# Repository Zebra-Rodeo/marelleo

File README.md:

# Marelleo

**English** · [Français](README.fr.md)

A box that plays a story when a child puts a figurine on top. No screen, no
account, no subscription, and nothing that leaves the house.

I built it for my three kids knowing nothing about electronics when I started.
Everything is here to rebuild it: the files to print, the board's manufacturing
files, the code, and enough guidance to get through it if you have never
soldered.

The story of the project, mistakes included, is written up here:
**[zebra.rodeo/en/blog/marelleo](https://zebra.rodeo/en/blog/marelleo/)**

---

## What it does

An NFC sticker is glued under a figurine. You put it on the engraved circle,
the box reads the sticker and plays whatever is associated with it: a file, a
list of files, or a live radio stream. Take the figurine off and the sound
carries on, or stops, depending on the setting.

Everything is configured from a browser, on the home WiFi, at
`http://marelleo.local`. Nothing to install. The box fetches its own updates.

| Gesture | Effect |
|---|---|
| Put a figurine on | plays its list |
| Put the same one back | resumes if it was paused |
| Short press | pause, resume, or restart a finished list |
| Long press | next track |
| Knob | volume, and power off at the click at the bottom of its travel |

Formats played: MP3 and M4A. The stories live on a microSD card.

---

## Two ways to build it

**On breadboard and perfboard**, with off-the-shelf modules. This is where to
start: you get it wrong, you unplug, you start again, and nothing is damaged.
Not a single solder joint for the first version.

**On the printed board**, whose manufacturing files are in [`carte/`](carte/).
Five assembled boards cost about 160 euros from JLCPCB, so 32 euros a board
with components placed. It is cleaner, smaller, and it lasts.

The same firmware runs on both: `pio run -e boite` for the modules,
`pio run -e carte` for the printed board.

---

## What to buy

### Module version, to start with

| Role | Part | Ballpark price |
|---|---|---|
| Brains | [ESP32-S3-DevKitC-1](https://www.amazon.fr/s?k=esp32+s3+devkitc) **N16R8** | 15 € |
| NFC reader | PN532, the red board, **in serial mode (HSU)** | 10 € |
| Audio | MAX98357A, I2S converter and amplifier | 7 € |
| Speaker | Visaton FRS 7, 4 Ω | 15 € |
| Power | Lipo Rider Plus, or any 5 V charging module | 12 € |
| Volume | 10 kΩ potentiometer **with a switch** | 3 € |
| Tags | NTAG213 25 mm, **on-metal** type | 10 € for 20 |
| Prototyping | [breadboard](https://www.amazon.fr/s?k=breadboard) and Dupont wires | 10 € |

The PN532 ships configured for I2C: there are two small switches on the board,
set them to **HSU**. It is printed on the back.

### Pinout, module version

| GPIO | To |
|---|---|
| `4` | amplifier `SD`, mutes the hiss at idle |
| `5` `6` `7` | amplifier `BCLK` `LRC` `DIN` |
| `8` `9` | PN532 `TXD` `RXD` |
| `11` `12` `13` `14` | SD card `CS` `SCK` `MOSI` `MISO` |
| `10` | potentiometer wiper, **must be on ADC1** |
| `18` | button |
| `48` | onboard LED |

The potentiometer has to sit on an ADC1 pin, that is to say `1` to `10`: the
ESP32-S3's ADC2 goes mute as soon as WiFi comes up, and the volume starts
jumping around for no visible reason.

---

## The enclosure

Three parts in [`boitier/`](boitier/), to print in PLA:

| File | Size | Notes |
|---|---|---|
| `marelleo-corps.stl` | 120 × 120 × 80 mm | the cube, raised name and engraved landing circle |
| `marelleo-base.stl` | 120 × 120 × 29 mm | the bottom, which carries the board and the battery |
| `marelleo-molette.stl` | 24 × 24 × 12 mm | the volume knob |

Printed on a Bambu Lab A1, 0.4 nozzle, 0.2 layers, three walls, 15 % infill.
The body goes on the plate open face up: no supports needed.

The PN532's antenna sits right under the engraved circle. Its range goes
through 3 mm of PLA without trouble.

**Do not screw straight into the plastic.** It holds once, twice, and on the
third go the part splits along the layers. Use **M3 brass inserts**: set one on
the hole, come down on it with the tip of the soldering iron, the brass melts
the plastic around itself and sinks in. You get a metal thread you can undo a
hundred times.

---

## The board

Everything is in [`carte/`](carte/):

- `marelleo-gerbers.zip`: upload as is to the manufacturer;
- `fab/marelleo-bom.csv` and `fab/marelleo-cpl.csv`: so JLCPCB can place the
  components;
- `composants.csv`: the readable list, with LCSC part numbers;
- `marelleo.kicad_pcb`: the board itself, if you want to modify it;
- `generer.py`: the script that draws it, because the board is generated
  rather than clicked;
- [`schema.md`](carte/schema.md): **read this before ordering.** The choices,
  the bench measurements, and the traps that cost me evenings.

Order from [JLCPCB](https://jlcpcb.com/): four layers, 1.6 mm, assembly on the
top side, standard and extended parts. Check LCSC stock on the day you order,
`stock.py` does it for you.

Two known deviations are documented in `schema.md`, including the `D1` diode
whose rotation has to be corrected by 180 degrees in their preview. Read it.

---

## The firmware

**It is written for this exact build.** The pinout lives in the code, not in a
configuration file: the two environments match my printed board and my module
prototype, and nothing else. If you wire it differently, a moved wire means a
constant to change at the top of `src/main.cpp`, and until that is done it will
not work, sometimes without saying anything. Start by reproducing the pinout
given above, and only move it afterwards.

And this is a weekend project, not a product. It runs every day at my house,
which is a sample of one box. There are rough edges left, cases nobody has run
into, and things I would do differently if I rewrote it. Read it as a starting
point that works, not as a reference.

[PlatformIO](https://platformio.org/) does all the work.

```sh
cd firmware
pio run -e boite -t upload     # modules on perfboard
pio run -e carte -t upload     # printed board
pio device monitor
```

Both environments compile the same code. What changes is the pinout, the flash
size and the PSRAM type, and mixing them up gives you a board that does not
start at all: `carte/schema.md` explains why.

### First start-up

The box knows no network when first powered on, so **it opens its own**, named
`Marelleo-XXXX`. A phone that connects to it brings up the setup page on its
own, like in a hotel. You pick the home WiFi there, and the box restarts on it.

After that, `http://marelleo.local` from any device on the network.

Button held for three seconds at power-on: the WiFi credentials are erased and
the box reopens its portal. That is the way out for a box that moves house, or
that you give away.

### Updates

The firmware compiled here fetches the versions published on
`maj.marelleo.org`, which are mine. A new version gets three start-ups to prove
itself: if it cannot find the network, the box goes back to the previous one on
its own.

**If you modify the code, change `MAJ_SOURCE_DEFAUT` in
`firmware/src/version.h`**, otherwise the box will replace your version with
mine at the first check.

---

## The figurines

Any object will do: a wooden figure, a toy car, a token, a flat pebble. Glue a
25 mm NTAG213 tag under its feet, the **on-metal** type if the object contains
any metal.

Put the figurine on the box, open `http://marelleo.local`, and it appears at
the top of the list. Give it a name, send files or search for a podcast, and
that is it. A figurine carries stories or a radio, never both.

---

## Licence

MIT, for the code as well as the manufacturing files. Build it, change it, sell
it, give it away. If you make something out of it, I would love to see it.

Marelleo, from *marelle*, the French word for hopscotch, the game where you
move forward by putting a foot down on a square. But mostly from **Mar**ceau,
**Ell**a and L**éo**nie, to whom the box belongs.

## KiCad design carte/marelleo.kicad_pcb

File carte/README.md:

# The board

**English** · [Français](README.fr.md)

Four layers, 1.6 mm, 60 × 70 mm. The files are ready to order.

| File | Role |
|---|---|
| `marelleo-gerbers.zip` | upload as is to the manufacturer |
| `fab/marelleo-bom.csv` | the bill of materials, JLCPCB format |
| `fab/marelleo-cpl.csv` | the component positions, JLCPCB format |
| `composants.csv` | the same list, readable, with LCSC part numbers |
| `marelleo.kicad_pcb` | the board itself, to modify it |
| `generer.py` | the script that draws it: the board is generated, not clicked |
| `stock.py` | checks LCSC stock on the day you order |
| `schema.md` | **read it before ordering** |

`schema.md` carries the choices, the measurements taken at the bench and the
traps that cost me evenings: the charger that suspends charging when you turn
the box off, the NFC module that blinks instead of starting, the diode whose
rotation has to be corrected by 180 degrees in JLCPCB's preview.

Five assembled boards came to about 160 euros, so 32 euros a board with
components placed.

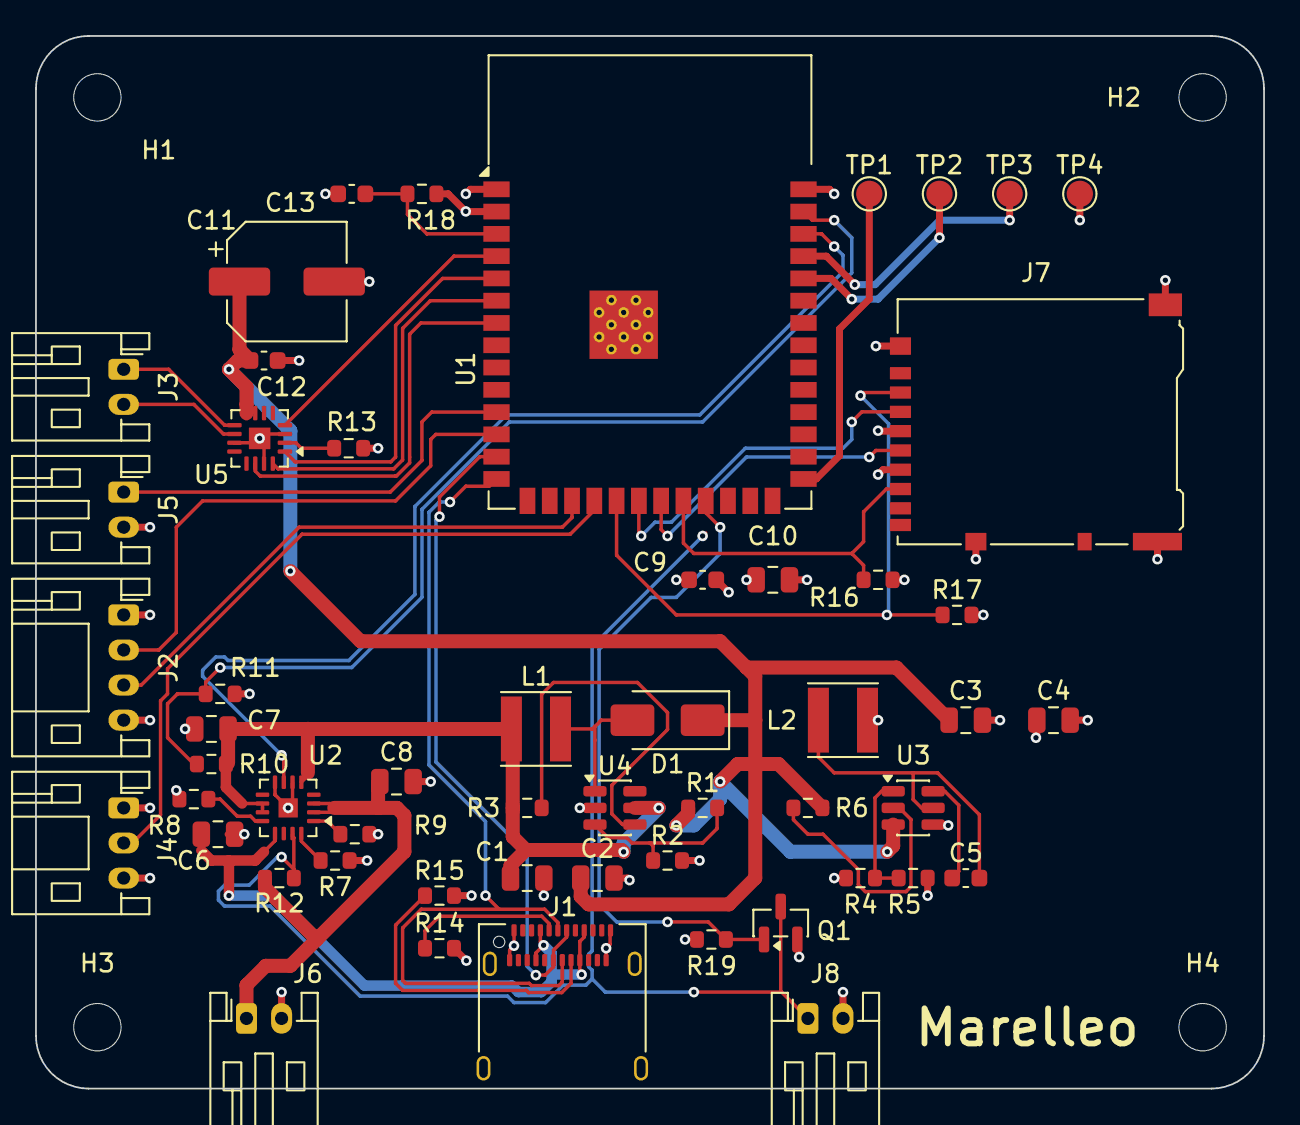
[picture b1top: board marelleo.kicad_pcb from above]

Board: 4 copper layers, 70.0 x 60.0 mm, 57 parts (0 on the bottom side), 43 nets.

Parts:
C1, C2, C4: 22 uF; C_0805_2012Metric
C3, C6, C7, C8, C10: 10 uF; C_0805_2012Metric
C5, C9, C12: 100 nF; C_0603_1608Metric
C11: 470 uF; CP_Elec_6.3x7.7
C13: 1 uF; C_0603_1608Metric
D1: SS34; D_SMA
H1, H2, H3, H4: M2.5; MountingHole_2.7mm_M2.5
J1: USB-C, charge et mise a jour; USB_C_Receptacle_Amphenol_12401610E4-2A
J2: vers le lecteur NFC deporte; JST_PH_S4B-PH-K_1x04_P2.00mm_Horizontal
J3: haut-parleurs; JST_PH_S2B-PH-K_1x02_P2.00mm_Horizontal
J4: potentiometre de volume; JST_PH_S3B-PH-K_1x03_P2.00mm_Horizontal
J5: bouton; JST_PH_S2B-PH-K_1x02_P2.00mm_Horizontal
J6: batterie; JST_PH_S2B-PH-K_1x02_P2.00mm_Horizontal
J7: connecteur microSD; microSD_HC_Hirose_DM3AT-SF-PEJM5
J8: interrupteur du potentiometre; JST_PH_S2B-PH-K_1x02_P2.00mm_Horizontal
L1, L2: 4,7 uH; L_Taiyo-Yuden_MD-4040
Q1: 2N7002; SOT-23
R1: 75 k; R_0603_1608Metric
R2, R9, R16, R17, R18: 10 k; R_0603_1608Metric
R3, R6, R10, R11, R19: 100 k; R_0603_1608Metric
R4: 0 R; R_0603_1608Metric
R5, R13: NP; R_0603_1608Metric
R7: 1 k; R_0603_1608Metric
R8: 1,5 k; R_0603_1608Metric
R12: 1 M; R_0603_1608Metric
R14, R15: 5,1 k; R_0603_1608Metric
TP1: TEST_IO0; TestPoint_Pad_D1.5mm
TP2: TEST_RX; TestPoint_Pad_D1.5mm
TP3: TEST_TX; TestPoint_Pad_D1.5mm
TP4: GND; TestPoint_Pad_D1.5mm
U1: ESP32-S3-WROOM-1-N8R2; ESP32-S3-WROOM-1
U2: BQ24075RGT, chargeur a chemin d'alimentation; VQFN-16-1EP_3x3mm_P0.5mm_EP1.1x1.1mm
U3: AP63203WU, abaisseur 3V3; TSOT-23-6
U4: MT3608, elevateur 5V; SOT-23-6
U5: MAX98357A; TQFN-16-1EP_3x3mm_P0.5mm_EP1.23x1.23mm

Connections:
+3V3: C4.1, C9.1, C10.1, J2.1, J4.1, J7.4, L2.2, R4.1, R16.2, R17.2, R18.2, U1.2
+5V: C2.1, C3.1, C11.1, C12.1, D1.1, R1.1, R6.2, U3.3, U5.7, U5.8
AMPLI_ARRET: U1.4, U5.4
AMPLI_GAIN: R13.1, U5.2
ARRET: J8.1, Q1.3, R12.1, U2.15
ARRET_CMD: Q1.1, R19.1, U1.23
BOUTON: J5.1, U1.11
BST_3V3: C5.1, U3.6
EN_3V3: R6.1, U3.2
EN_5V: R3.1, U4.4
FB_3V3: R4.2, R5.1, U3.1
FB_5V: R1.2, R2.1, U4.3
GND: C1.2, C2.2, C3.2, C4.2, C6.2, C7.2, C8.2, C9.2, C10.2, C11.2, C12.2, C13.2, J1.A1, J1.A12, J1.B1, J1.B12, J1.SH, J2.4, J4.3, J5.2, J6.2, J7.6, J7.SH, J8.2, Q1.2, R2.2, R5.2, R7.2, R8.2, R9.2, R11.2, R13.2, R14.2, R15.2, R19.2, TP4.1, U1.1, U1.40, U1.41, U2.6, U2.8, U2.17, U3.4, U4.2, U5.3, U5.11, U5.15, U5.17
HP_MOINS: J3.2, U5.10
HP_PLUS: J3.1, U5.9
I2S_BCLK: U1.6, U5.16
I2S_DIN: U1.5, U5.1
I2S_LRCLK: U1.7, U5.14
ILIM: R8.1, U2.12
ISET: R7.1, U2.16
NFC_RX: J2.2, U1.12
NFC_TX: J2.3, U1.17
NIVEAU_BATTERIE: R10.2, R11.1, U1.39
RESET: C13.1, R18.1, U1.3
SD_CLK: J7.5, U1.21
SD_CS: J7.2, R17.1, U1.19
SD_MISO: J7.7, R16.1, U1.22
SD_MOSI: J7.3, U1.20
SW_3V3: C5.2, L2.1, U3.5
SW_5V: D1.2, L1.2, U4.1
TEST_IO0: TP1.1, U1.27
TEST_RX: TP2.1, U1.36
TEST_TX: TP3.1, U1.37
TS: R9.1, U2.1
USB_CC1: J1.A5, R14.1
USB_CC2: J1.B5, R15.1
USB_D+: J1.A6, J1.B6, U1.14
USB_D-: J1.A7, J1.B7, U1.13
USB_PRESENT: U1.38, U2.7
VBAT: C8.1, J6.1, R12.2, U2.2, U2.3
VBUS: C6.1, J1.A4, J1.A9, J1.B4, J1.B9, U2.13
VOLUME: J4.2, U1.18
VSYS: C1.1, C7.1, L1.1, R3.2, R10.1, U2.5, U2.10, U2.11, U4.5

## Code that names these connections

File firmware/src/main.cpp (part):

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// Les GPIO 11 a 14 sont sur l'ADC2, que le WiFi rend muet. Sans importance ici :
// le bus SPI s'en sert en numerique, jamais en analogique.
#ifdef CARTE_IMPRIMEE
constexpr uint8_t PIN_SD_CS = 11, PIN_SD_CLK = 13, PIN_SD_MOSI = 12, PIN_SD_MISO = 14;
#else
constexpr uint8_t PIN_SD_CS = 11, PIN_SD_CLK = 12, PIN_SD_MOSI = 13, PIN_SD_MISO = 14;
#endif
SPIClass spiSD(FSPI);
fs::FS*  contenu = nullptr;
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
bool monterStockage() {
  bool flash = LittleFS.begin();
  spiSD.begin(PIN_SD_CLK, PIN_SD_MISO, PIN_SD_MOSI, PIN_SD_CS);
  // 4 MHz, 1 MHz en repli pour monter. Des ecritures echouent au hasard :
  // `sdCommand(): token error [13] 0x33`, une reponse corrompue a SEND_STATUS
  // juste apres l'ecriture des secteurs. Un bit se retourne sur le fil, le
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  // pas.
  bool monte = false;
  for (int essai = 1; essai <= 3 && !monte; essai++) {
    monte = SD.begin(PIN_SD_CS, spiSD, 4000000) || SD.begin(PIN_SD_CS, spiSD, 1000000);
    if (monte) break;
    Serial.printf("carte SD : montage refuse, essai %d sur 3\n", essai);
    SD.end();
    spiSD.end();
    delay(200);
    spiSD.begin(PIN_SD_CLK, PIN_SD_MISO, PIN_SD_MOSI, PIN_SD_CS);
  }
  if (monte) {
    contenu = &SD;       contenuSurSD = true;
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// pastilles. On l'active par -DCARTE_IMPRIMEE, voir l'environnement "carte"
// dans platformio.ini.
#ifdef CARTE_IMPRIMEE
constexpr uint8_t PIN_I2S_BCLK = 6, PIN_I2S_LRC = 7, PIN_I2S_DOUT = 5;
#else
constexpr uint8_t PIN_I2S_BCLK = 5, PIN_I2S_LRC = 6, PIN_I2S_DOUT = 7;
#endif
constexpr uint8_t PIN_AMP_SD   = 4;
constexpr uint8_t PIN_NFC_RX   = 8, PIN_NFC_TX = 9;
// La jauge n'existe que sur la carte imprimee : IO1 voit VSYS a travers un pont
// de deux 100 k, et IO2 recoit PGOOD du chargeur. Le prototype n'a ni l'un ni
// l'autre, d'ou 255, qui veut dire « pas de mesure » plutot qu'un chiffre faux.
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// Le verrou d'extinction : la grille de Q1, qui tire SYSOFF a la masse en
// parallele de l'interrupteur du potentiometre. Haut maintient la boite
// alimentee, bas la laisse s'eteindre.
constexpr uint8_t PIN_ARRET = 21;
#else
constexpr uint8_t PIN_BATTERIE = 255, PIN_USB = 255, PIN_ARRET = 255;
#endif
// Le potentiometre doit etre sur l'ADC1 (GPIO 1 a 10) : l'ADC2 de l'ESP32-S3
// devient muet des que le WiFi est actif.
constexpr uint8_t PIN_POT = 10, PIN_BOUTON = 18;   // GPIO 15, 16 et 17 libres
constexpr uint8_t PIN_LED      = 48;

// La mise en veille se decide sur le NIVEAU de volume, pas sur la valeur brute
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RTC_DATA_ATTR bool adieuDit = false;

Audio      audio;
Pn532Hsu   nfc(Serial1, PIN_NFC_RX, PIN_NFC_TX);
Library    biblio;
Commandes  commandes;
Batterie   batterie;
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String   dernierBadge;   // derniere figurine badgee, connue ou non : celle que la page configure
uint8_t  absences = 0;
uint32_t derniereScrutation = 0;
uint8_t  volume = 0;     // toujours dicte par la position du potentiometre

String enHex(const uint8_t* uid, uint8_t len) {
  char b[16] = {0};
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  SD.end();
  spiSD.end();
  delay(20);
  spiSD.begin(PIN_SD_CLK, PIN_SD_MISO, PIN_SD_MOSI, PIN_SD_CS);
  bool ok = SD.begin(PIN_SD_CS, spiSD, 4000000) || SD.begin(PIN_SD_CS, spiSD, 1000000);
  Serial.printf("carte SD : remontage %s\n", ok ? "reussi" : "echoue");
  return ok;
}
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    }
  }

  commandes.begin(PIN_POT, PIN_BOUTON, VOLUME_MIN, VOLUME_MAX);
  volume = commandes.volume();
  Serial.printf("volume : %u  [%u-%u]  brut %u\n",
                volume, VOLUME_MIN, VOLUME_MAX, commandes.potBrut());
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  if (volume > VOLUME_MIN) adieuDit = false;
  if (!adieuDit) {
    digitalWrite(PIN_AMP_SD, HIGH);
    carillon(PIN_I2S_BCLK, PIN_I2S_LRC, PIN_I2S_DOUT, volume, VOLUME_MAX);
    digitalWrite(PIN_AMP_SD, LOW);
  }

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    // pour verifier qu'un fichier est bien decode, sans bavarder le reste du temps.
    else if (m.e == Audio::evt_info && m.msg) Serial.printf("audio : %s\n", m.msg);
  };
  audio.setPinout(PIN_I2S_BCLK, PIN_I2S_LRC, PIN_I2S_DOUT);
  audio.setVolume(volume);
  xTaskCreatePinnedToCore(tacheAudio, "audio", 8192, nullptr, 4, nullptr, 1);

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  // WiFi pour revenir au portail de configuration. La LED passe au bleu pendant
  // l'attente, et au blanc quand l'effacement est confirme.
  bool effacer = false;
  pinMode(PIN_BOUTON, INPUT_PULLUP);
  if (digitalRead(PIN_BOUTON) == LOW) {
    led(0, 0, 30);
    uint32_t debut = millis();
    while (digitalRead(PIN_BOUTON) == LOW && millis() - debut < 3000) delay(20);
    effacer = millis() - debut >= 3000;
    led(effacer ? 20 : 0, effacer ? 20 : 0, effacer ? 20 : 0);
  }
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// meme apres le declic, ce qui lui laisse le temps de sonner. Lache, elle rend
// la main a l'interrupteur, et s'eteint donc pour de bon s'il est ouvert.
void verrou(bool tenu) {
  if (PIN_ARRET == 255) return;
  pinMode(PIN_ARRET, OUTPUT);
  digitalWrite(PIN_ARRET, tenu ? HIGH : LOW);
}

// Le geste d'extinction, entendu. L'amplificateur dort entre deux lectures : on
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void adieu() {
  if (lecture != Lecture::Arret) arreter("extinction");
  digitalWrite(PIN_AMP_SD, HIGH);
  carillonAdieu(PIN_I2S_BCLK, PIN_I2S_LRC, PIN_I2S_DOUT, commandes.volume(), VOLUME_MAX);
  digitalWrite(PIN_AMP_SD, LOW);
}

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  // Sans verrou, sur le prototype, le declic coupe tout avant qu'on ait pu
  // dire quoi que ce soit : on laisse alors la boite tranquille.
  static uint32_t basDepuis = 0;
  const bool enBas = commandes.volume() == VOLUME_MIN;
  const bool peutSaluer = PIN_ARRET != 255 || batterie.surSecteur();
  if (enBas && peutSaluer) {
    if (!basDepuis) { basDepuis = millis(); verrou(true); }
    else if (!adieuDit && millis() - basDepuis > VEILLE_STABLE_MS) {
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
